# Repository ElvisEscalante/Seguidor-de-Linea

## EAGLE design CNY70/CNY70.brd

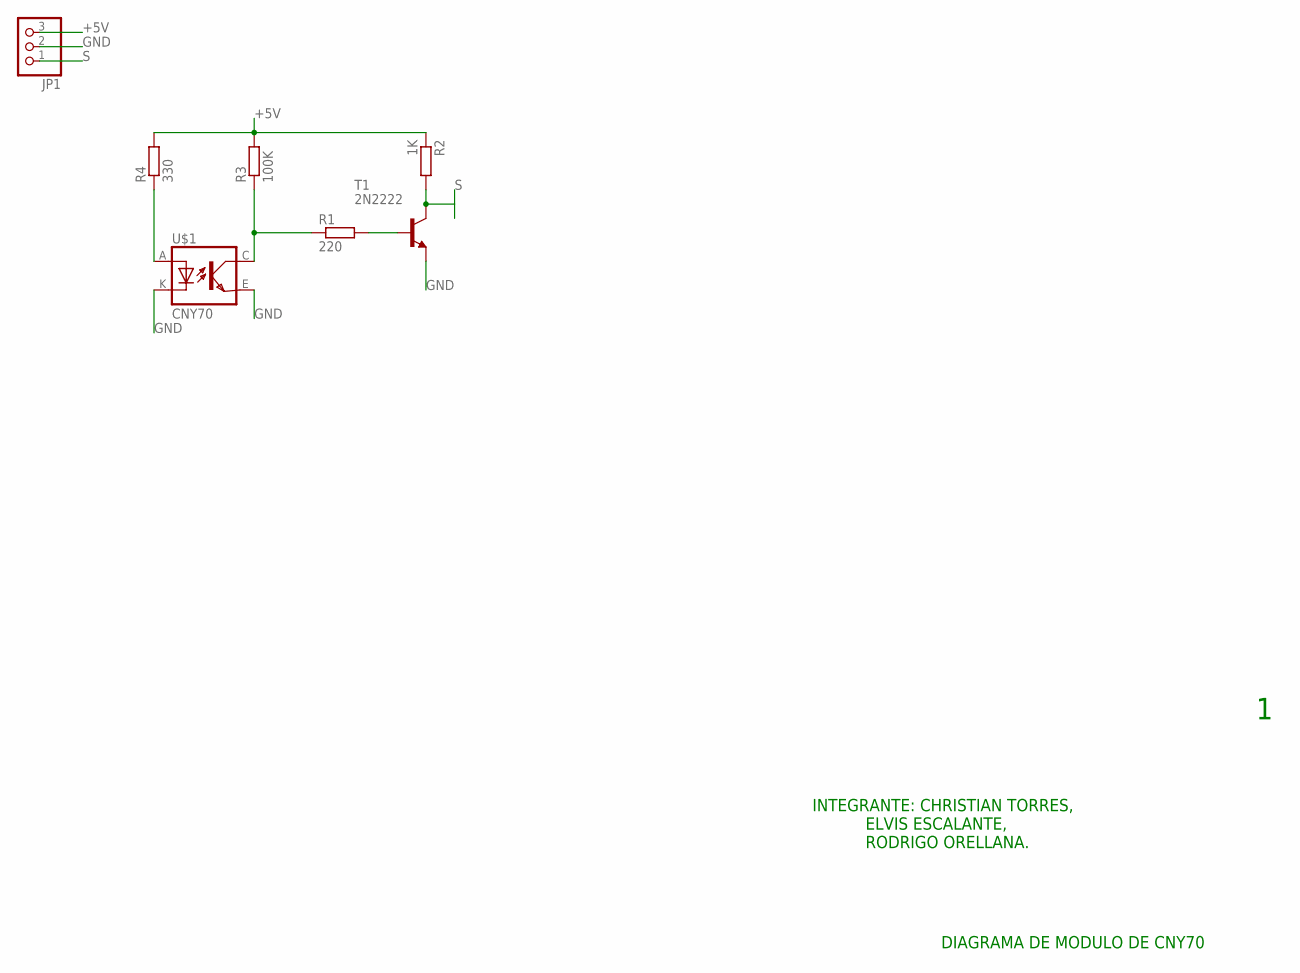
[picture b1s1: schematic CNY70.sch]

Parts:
JP1: PINHD-1X3; 1X03
R1: 220; 0207/12
R2: 1K; 0207/12
R3: 100K; 0207/12
R4: 330; 0207/12
T1: 2N2222; TO92
U$1: CNY70; 4

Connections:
+5V: JP1.3, R2.1, R3.2, R4.2
GND: JP1.2, T1.3 (E), U$1.E (EMI), U$1.K (C)
unnamed: R4.1, U$1.A
unnamed: R1.1, R3.1, U$1.C (COL)
unnamed: R1.2, T1.1 (B)
S: JP1.1, R2.2, T1.2 (C)

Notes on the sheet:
DIAGRAMA DE MODULO DE CNY70
INTEGRANTE: CHRISTIAN TORRES, ELVIS ESCALANTE, RODRIGO ORELLANA.

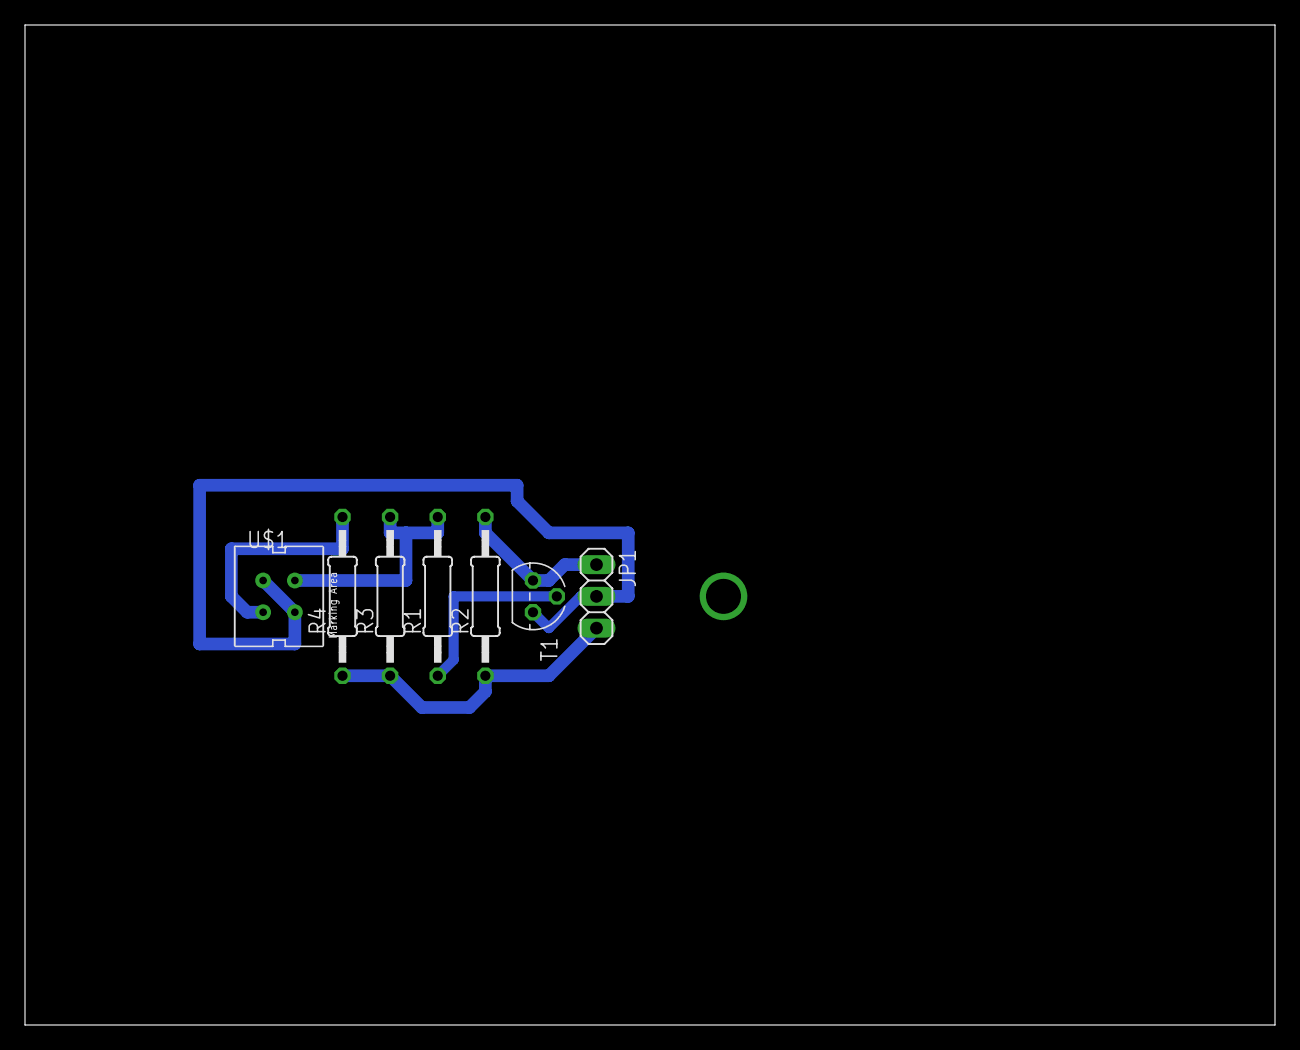
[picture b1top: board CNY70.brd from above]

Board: 2 copper layers, 100.0 x 80.0 mm, 7 parts (0 on the bottom side), 6 nets.
